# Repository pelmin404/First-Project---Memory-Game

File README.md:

# First-Project_Memory-Game

A small circuit board Simon type game based on Arduino's ATmega328P

This game is made to improve short term memory under load and just to spend time when bored.

# 🛠️ Technical Details
### The MCU is programmed with an internal 8 MHz clock

It works on the same MCU found in Arduino UNO R3 and a few others. It can be powered by a DC power source ranging from 7 to 35 volts, the files provided use a 9V input as an example. In the final iteration I added a power indicator with a MOSFET and an LED which is brighter the higher the input voltage with 9 volts being barely visible in order to indicate when the battery is almost at 7 volts, which may cause MCU instability. In order for the indicator system to work properly the combined voltage drop of the indicator LED and the following diode D6 should be as close as possible to the drop of the L7805CV or about 2 volts. The sound control potentiometer can be either logarithmic or regular, depending on preference. The small button on the top left corner of the board is used to reset the MCU and therefore the game if you encounter an electrical issue causing MCU instability or just really don't want to lose. The circular solder pad for the power source is ground (-).

## ⚠️ Please note that some mechanical switches may produce a noisy signal that forces the MCU to think you pressed the button multiple times

# 📼 Video examples

[Win example](https://github.com/pelmin404/First-Project_Memory-Game/blob/main/Videos/Win%20example.mp4)

[Loss example](https://github.com/pelmin404/First-Project_Memory-Game/blob/main/Videos/Loss%20example.mp4)

[Power indicator](https://github.com/pelmin404/First-Project_Memory-Game/blob/main/Videos/Power%20indicator.mp4)

# ⚙️ Part List

- [ATMEGA328P-PU](https://www.digikey.com/en/products/detail/microchip-technology/ATMEGA328P-PU/1914589)
- [MCU socket](https://www.digikey.com/en/products/detail/3m/4828-3004-CP/1133633?s=N4IgTCBcDaIMwFkCsAWAHABgLQDkAiIAugL5A)
- [Leo Sales Ltd. 10mm 2x6 Colors LED](https://www.microcenter.com/product/511285/leo-sales-ltd-10mm-2x6-colors-led)
- [Tactile Button Assortment](https://www.microcenter.com/product/427684/tactile-button-assortment)
- [L7805CV]()
- [5V 1.5A Linear Voltage Regulator - 7805 TO-220](https://www.adafruit.com/product/2164)
- 5 10 kΩ resistors
- 4 220 Ω resistors
- 1 22 kΩ resistor
- 1 0.33 μF capacitor
- 1 0.1 μF capacitor
- [Leo Sales Ltd. PCB Mounted Piezo Buzzer - 9x5.5mm (10 Pack)](https://www.microcenter.com/product/677928/leo-sales-ltd-pcb-mounted-piezo-buzzer-9x55mm-(10-pack))
- A 10 kΩ potentiometer, I used an ACP CA9-V10 footprint
- A 6 mm THT momentary push button
- Any 5 mm LED and a diode that fits the footprint, that have a total voltage drop of 2 V

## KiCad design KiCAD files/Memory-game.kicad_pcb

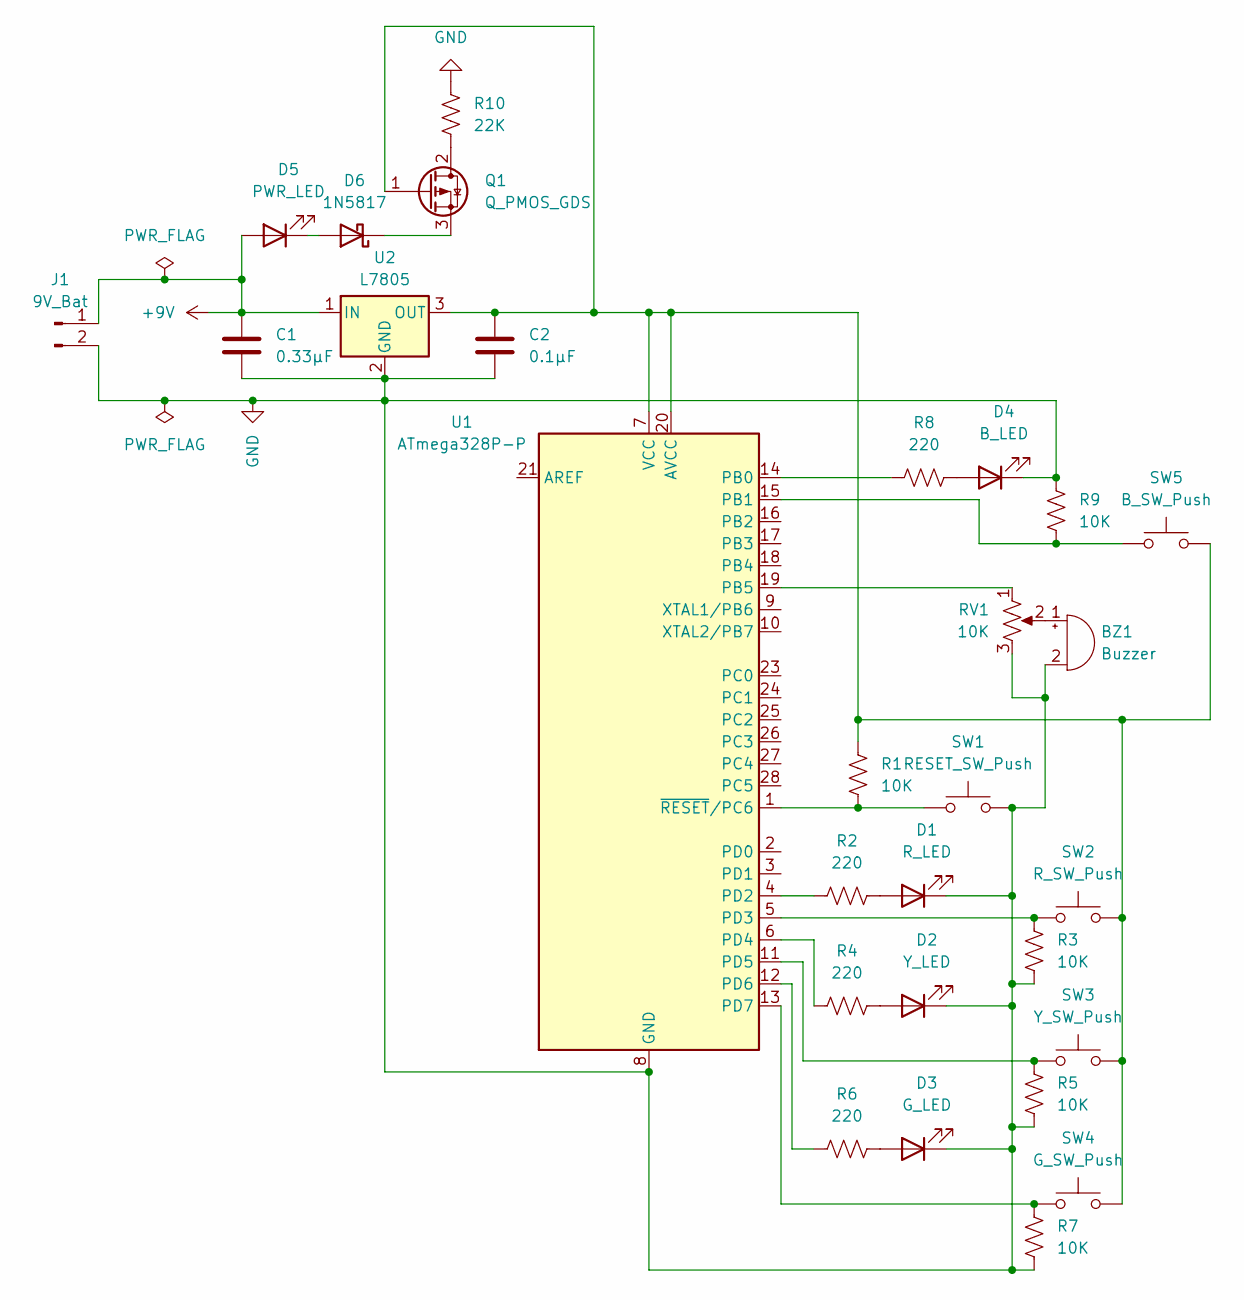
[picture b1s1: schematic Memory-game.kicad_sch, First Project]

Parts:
BZ1: Buzzer; MagneticBuzzer_PUI_AT-0927-TT-6-R
C1: 0.33µF; C_Disc_D4.7mm_W2.5mm_P5.00mm
C2: 0.1µF; C_Disc_D4.7mm_W2.5mm_P5.00mm
D1: R_LED; LED_D10.0mm
D2: Y_LED; LED_D10.0mm
D3: G_LED; LED_D10.0mm
D4: B_LED; LED_D10.0mm
D5: PWR_LED; LED_D5.0mm
D6: 1N5817; D_DO-41_SOD81_P10.16mm_Horizontal
J1: 9V_Bat; SolderWire-0.1sqmm_1x02_P3.6mm_D0.4mm_OD1mm
Q1: Q_PMOS_GDS; TO-220-3_Horizontal_TabDown
R1, R3, R5, R7, R9: 10K; R_Axial_DIN0207_L6.3mm_D2.5mm_P7.62mm_Horizontal
R2, R4, R6, R8: 220; R_Axial_DIN0207_L6.3mm_D2.5mm_P7.62mm_Horizontal
R10: 22K; R_Axial_DIN0207_L6.3mm_D2.5mm_P7.62mm_Horizontal
RV1: 10K; Potentiometer_ACP_CA9-V10_Vertical
SW1: RESET_SW_Push; SW_PUSH_6mm
SW2: R_SW_Push; SW_PUSH-12mm
SW3: Y_SW_Push; SW_PUSH-12mm
SW4: G_SW_Push; SW_PUSH-12mm
SW5: B_SW_Push; SW_PUSH-12mm
U1: ATmega328P-P; DIP-28_W7.62mm_Socket
U2: L7805; TO-220-3_Horizontal_TabDown

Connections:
+9V: C1.2, D5.2 (A), J1.1, U2.1 (IN)
GND: BZ1.2 (-), C1.1, C2.2, D1.1 (K), D2.1 (K), D3.1 (K), D4.1 (K), J1.2, R3.2, R5.2, R7.2, R9.2, R10.1, RV1.3, SW1.2, U1.8 (GND), U1.22 (GND), U2.2 (GND)
unnamed: BZ1.1 (+), RV1.2
unnamed: D1.2 (A), R2.1
unnamed: D2.2 (A), R4.1
unnamed: D3.2 (A), R6.1
unnamed: D4.2 (A), R8.1
unnamed: D5.1 (K), D6.2 (A)
unnamed: D6.1 (K), Q1.3 (S)
unnamed: Q1.2 (D), R10.2
unnamed: C2.1, Q1.1 (G), R1.1, SW2.2, SW3.2, SW4.2, SW5.2, U1.7 (VCC), U1.20 (AVCC), U2.3 (OUT)
unnamed: R8.2, U1.14 (PB0)
unnamed: R9.1, SW5.1, U1.15 (PB1)
unnamed: RV1.1, U1.19 (PB5)
unnamed: R2.2, U1.4 (PD2)
unnamed: R3.1, SW2.1, U1.5 (PD3)
unnamed: R4.2, U1.6 (PD4)
unnamed: R5.1, SW3.1, U1.11 (PD5)
unnamed: R6.2, U1.12 (PD6)
unnamed: R7.1, SW4.1, U1.13 (PD7)
unnamed: R1.2, SW1.1, U1.1 (~RESET/PC6)

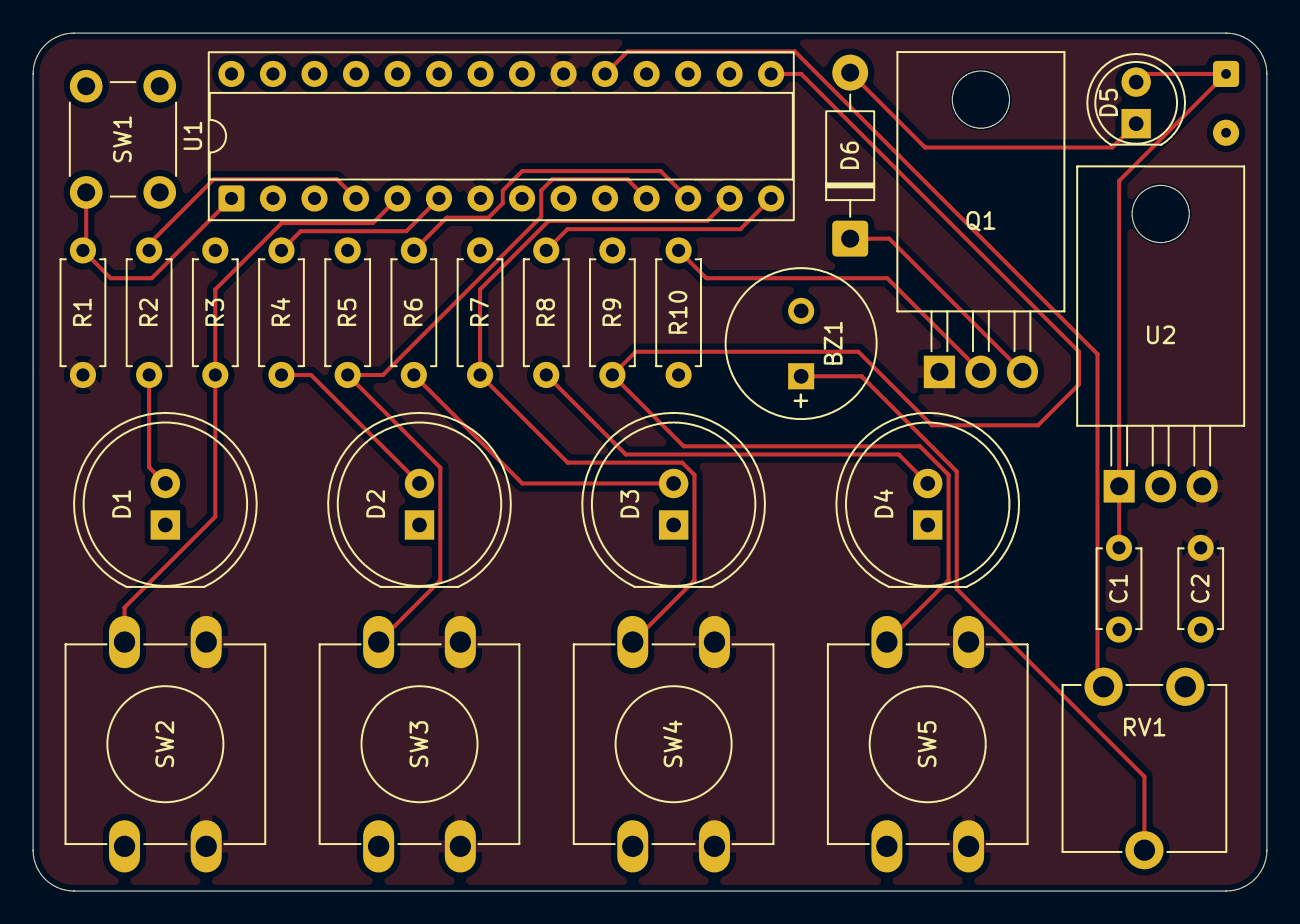
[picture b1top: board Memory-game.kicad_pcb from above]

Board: 2 copper layers, 75.5 x 52.5 mm, 29 parts (0 on the bottom side), 21 nets.
